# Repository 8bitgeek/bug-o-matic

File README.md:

# bug-o-matic
[Bug-O-Matic](http://www.8bitgeek.net/bug-o-matic) Open Hardware USB Debugger Featuring JTAG/SWD/UART/I2C/GPIO 

# Setting up a working copy of the repository

```
git clone https://github.com/8bitgeek/bug-o-matic.git
cd bug-o-matic
git submodule init
git submodule update --recursive
```

# Documentation

Bug over to [Hardware](https://github.com/8bitgeek/bug-o-matic/tree/master/hw) or [Firmware](https://github.com/8bitgeek/bug-o-matic/tree/master/fw) for more documentation and HOWTO.

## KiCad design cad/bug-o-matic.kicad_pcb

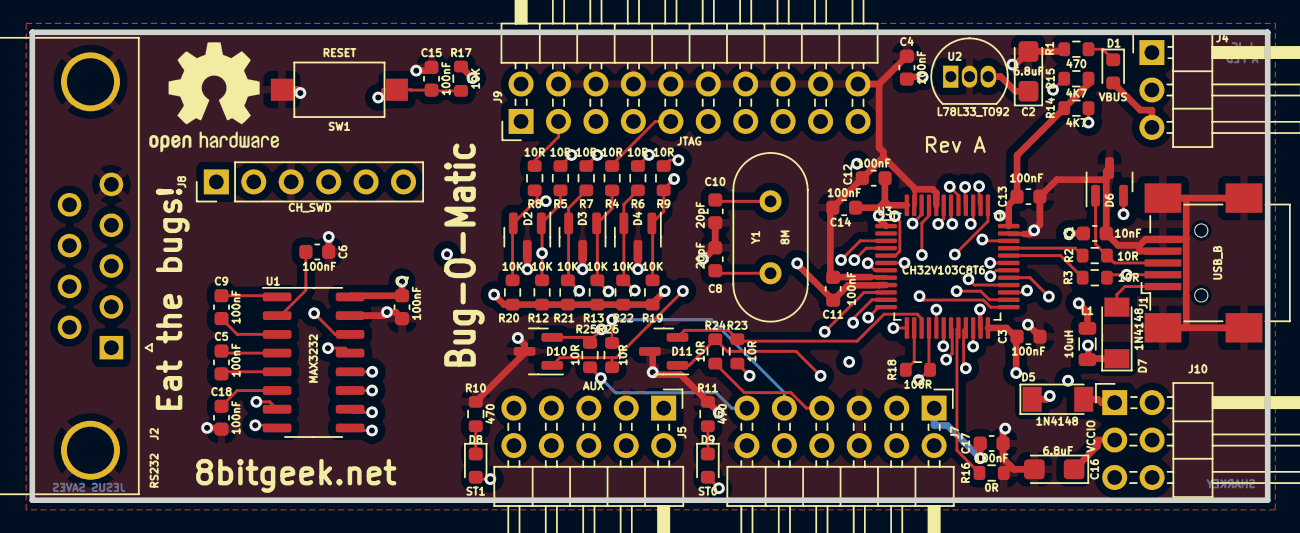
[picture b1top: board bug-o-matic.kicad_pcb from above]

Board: 4 copper layers, 83.8 x 31.8 mm, 71 parts (1 on the bottom side), 73 nets.

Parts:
C1: 10nF; C_0603_1608Metric
C2, C16: 6.8uF; CP_EIA-3216-18_Kemet-A
C3, C4, C5, C6, C7, C9, C11, C12, C13, C14, C15, C17, C18: 100nF; C_0603_1608Metric
C8, C10: 20pF; C_0603_1608Metric
D1: VBUS; LED_0603_1608Metric
D2, D3, D4, D6, D10, D11: NUP2105L; SOT-23
D5, D7: 1N4148; D_MiniMELF
D8: ST1; LED_0603_1608Metric
D9: ST0; LED_0603_1608Metric
J1: USB_B; USB_Mini-B_Wuerth_65100516121_Horizontal
J2: RS232; DSUB-9_Female_Horizontal_P2.77x2.84mm_EdgePinOffset7.70mm_H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
J4: VOUT; PinHeader_1x03_P2.54mm_Horizontal
J5: AUX; PinHeader_2x05_P2.54mm_Horizontal
J7: SWD/SERIAL; PinHeader_2x06_P2.54mm_Horizontal
J8: CH_SWD; PinHeader_1x06_P2.54mm_Vertical
J9: JTAG; PinHeader_2x10_P2.54mm_Horizontal
J10: VCCIO; PinHeader_2x03_P2.54mm_Horizontal
L1: 10uH; L_0805_2012Metric
R1, R10, R11: 470; R_0603_1608Metric
R2, R3, R4, R5, R6, R7, R8, R9, R23, R24, R25, R26: 10R; R_0603_1608Metric
R12, R13, R17, R19, R20, R21, R22: 10K; R_0603_1608Metric
R14, R15: 4K7; R_0603_1608Metric
R16: 0R; R_0603_1608Metric
R18: 100R; R_0603_1608Metric
REF1, REF2: OSHW-Logo2_9.8x8mm_SilkScreen
SW1: RESET; SW_SPST_CK_RS282G05A3
U1: MAX3232; SOIC-16_3.9x9.9mm_P1.27mm
U2: L78L33_TO92; TO-92_Inline
U3: CH32V103C8T6; LQFP-48_7x7mm_P0.5mm
Y1: 8M; Crystal_HC49-4H_Vertical

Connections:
+3V3: C4.1, J4.1, J5.1, U2.1 (VO)
+5V: C2.1, D1.2 (A), J4.3, J5.2, L1.2, U2.3 (VI)
+VSW: C3.1, C7.1, C11.1, C12.1, C13.1, C14.1, C16.1, J8.1, J10.3, R12.1, R13.1, R14.1, R15.1, R17.1, R19.1, R20.1, R21.1, R22.1, U1.16 (VCC), U3.1 (VBAT), U3.9 (VDDA), U3.24 (VDD), U3.36 (VDD), U3.48 (VDD)
/AUX0: J5.10, U3.17 (PA7)
/AUX1: J5.9, U3.29 (PA8)
/AUX2: J5.8, U3.30 (PA9)
/AUX3: J5.7, U3.18 (PB0)
/AUX4: J5.6, U3.19 (PB1)
/AUX5: J5.5, U3.45 (PB8)
/AUX6: J5.4, U3.46 (PB9)
/BOOT1: R16.1, U3.20 (PB2)
/CH_NRST: C15.1, J8.5, R17.2, SW1.1, U3.7 (NRST)
/CH_SWCLK: J8.2, U3.38 (PA15)
/CH_SWDIO: J8.4, U3.34 (PA13)
/CH_SWO: J8.6, U3.39 (PB3)
/CTS: J2.7, U1.8 (R2IN)
/I2C_SCL: J7.8, R14.2, U3.42 (PB6)
/I2C_SDA: J7.10, R15.2, U3.43 (PB7)
/MCU-SRST: D4.1 (K), R9.2, R19.2, U3.40 (PB4)
/MCU-TCK: D3.1 (K), R4.2, R13.2, U3.26 (PB13)
/MCU-TDI: D2.1 (K), R5.2, R12.2, U3.27 (PB14)
/MCU-TDO: D4.2 (K), R6.2, R22.2, U3.28 (PB15)
/MCU-TMS: D3.2 (K), R7.2, R21.2, U3.25 (PB12)
/MCU-TRST: D2.2 (K), R8.2, R20.2, U3.41 (PB5)
/MCU_RS232_CTS: U1.9 (R2OUT), U3.10 (PA0)
/MCU_RS232_RTS: U1.10 (T2IN), U3.11 (PA1)
/MCU_RS232_RX: U1.12 (R1OUT), U3.13 (PA3)
/MCU_RS232_TX: U1.11 (T1IN), U3.12 (PA2)
/MCU_SWCLK: D11.2 (K), R23.2, U3.15 (PA5)
/MCU_SWDIO: D11.1 (K), R18.1, R24.2, U3.16 (PA6)
/MCU_SWDIO_PUD: R18.2, U3.14 (PA4)
/MCU_SWNRST: D10.1 (K), R26.2, U3.37 (PA14)
/MCU_SWO: D10.2 (K), R25.2, U3.31 (PA10)
/NRST: J7.9, R26.1
/RTS: J2.8, U1.7 (T2OUT)
/RXD: J2.3, U1.13 (R1IN)
/SRST: J9.15, R9.1
/ST0: D8.2 (A), U3.3 (PC14)
/ST1: D9.2 (A), U3.4 (PC15)
/SWCLK: J7.3, R23.1
/SWDIO: J7.7, R24.1
/SWO: J7.11, R25.1
/TCK: J9.9, R4.1
/TDI: J9.5, R5.1
/TDO: J9.13, R6.1
/TMS: J9.7, R7.1
/TRST: J9.3, R8.1
/TXD: J2.2, U1.14 (T1OUT)
/UART_RX: J7.4, U3.22 (PB11)
/UART_TX: J7.2, U3.21 (PB10)
/UD+: R2.1, U3.33 (PA12)
/UD-: R3.1, U3.32 (PA11)
/VOUT: D5.2 (A), J4.2, J10.1
/VOUTR: D5.1 (K), J9.2, J10.2
/VSWD: C17.1, J7.1, J10.4
/VTARGET: J9.1, J10.5, J10.6
/VUSB: C1.1, D7.1 (K), L1.1
GND: C1.2, C2.2, C3.2, C4.2, C6.1, C7.2, C8.1, C10.1, C11.2, C12.2, C13.2, C14.2, C15.2, C16.2, C17.2, C18.1, D2.3 (A), D3.3 (A), D4.3 (A), D6.3 (A), D10.3 (A), D11.3 (A), J1.4 (GND), J1.5 (Shield), J2.0 (PAD), J2.5, J5.3, J7.5, J7.6, J7.12, J8.3, J9.4, J9.6, J9.8, J9.10, J9.12, J9.14, J9.16, J9.18, J9.20, R1.2, R10.2, R11.2, R16.2, SW1.2, U1.15 (GND), U2.2 (GND), U3.8 (VSSA), U3.23 (VSS), U3.35 (VSS), U3.44 (BOOT0), U3.47 (VSS)
unnamed: C18.2, U1.6 (VS-)
unnamed: D1.1 (K), R1.1
unnamed: D7.2 (A), J1.1 (VBUS)
unnamed: D8.1 (K), R10.1
unnamed: D9.1 (K), R11.1
unnamed: D6.1 (K), J1.3 (D+), R2.2
unnamed: D6.2 (K), J1.2 (D-), R3.2
unnamed: J2.1, J2.4, J2.6
unnamed: C9.2, U1.1 (C1+)
unnamed: C9.1, U1.3 (C1-)
unnamed: C5.1, U1.4 (C2+)
unnamed: C5.2, U1.5 (C2-)
unnamed: C6.2, U1.2 (VS+)
unnamed: C10.2, U3.5 (PD0), Y1.2
unnamed: C8.2, U3.6 (PD1), Y1.1

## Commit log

2022-07-29 4 layer routing
2022-07-29 preliminary artwork completed
2022-07-29 Revision A CAM generation
2022-08-16 sync submodules
2022-08-16 Removed submodule
2022-08-16 reffaccgtor files and folders for cook
2022-08-20 add submodule briscits-bsp
2022-08-20 Update READ with mcu pinouts
2022-08-20 Update README - MCU pinout corrections
2022-08-20 remove docs/pinouts file
2022-08-20 README urls
2022-08-20 fixup readme skeletons
2022-08-20 Re-org READMEs
2022-08-21 sync bug-o-matic briscits bsp
2022-08-21 README.md
